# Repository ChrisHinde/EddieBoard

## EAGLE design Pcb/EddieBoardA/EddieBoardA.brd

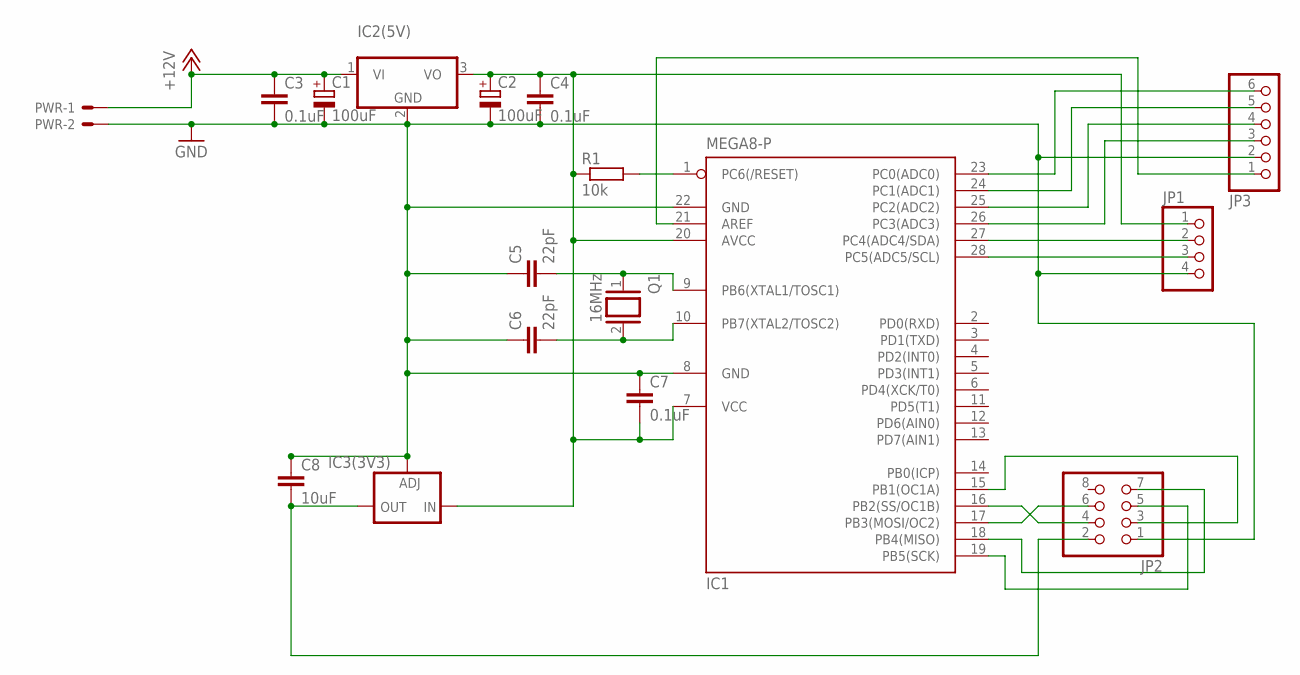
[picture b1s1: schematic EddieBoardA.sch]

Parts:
C1, C2: 100uF; E2,5-6
C3, C4, C7: 0.1uF; C025-025X050
C5, C6: 22pF; C025-025X050
C8: 10uF; C025-025X050
IC1: MEGA8-P; DIL28-3
IC2(5V): 7805TV; TO220V
IC3(3V3): LD117AV; TO220L1
JP1: PINHD-1X4; 1X04
JP2: PINHD-2X4; 2X04
JP3: PINHD-1X6; 1X06
PWR: 22-23-2021; MPN PWR
Q1: 16MHz; QS
R1: 10k; 0207/12

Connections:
+12V: C1.+, C3.1, IC2(5V).1 (VI), PWR.1
GND: C1.-, C2.-, C3.2, C4.2, C5.1, C6.1, C7.1, C8.1, IC1.8 (GND), IC1.22 (GND), IC2(5V).2 (GND), IC3(3V3).1 (ADJ), JP1.4, JP2.1, JP3.2, PWR.2
unnamed: IC1.1 (PC6(/RESET)), R1.2
unnamed: IC1.27 (PC4(ADC4/SDA)), JP1.2
unnamed: C5.2, IC1.9 (PB6(XTAL1/TOSC1)), Q1.1
unnamed: C6.2, IC1.10 (PB7(XTAL2/TOSC2)), Q1.2
unnamed: IC1.28 (PC5(ADC5/SCL)), JP1.3
unnamed: IC1.19 (PB5(SCK)), JP2.5
unnamed: IC1.15 (PB1(OC1A)), JP2.3
unnamed: IC1.17 (PB3(MOSI/OC2)), JP2.6
unnamed: IC1.16 (PB2(SS/OC1B)), JP2.4
unnamed: IC1.18 (PB4(MISO)), JP2.7
unnamed: IC1.21 (AREF), JP3.1
unnamed: IC1.26 (PC3(ADC3)), JP3.3
unnamed: IC1.25 (PC2(ADC2)), JP3.4
unnamed: IC1.24 (PC1(ADC1)), JP3.5
unnamed: IC1.23 (PC0(ADC0)), JP3.6
unnamed: C8.2, IC3(3V3).2 (OUT), JP2.2
VCC: C2.+, C4.1, C7.2, IC1.7 (VCC), IC1.20 (AVCC), IC2(5V).3 (VO), IC3(3V3).3 (IN), JP1.1, R1.1

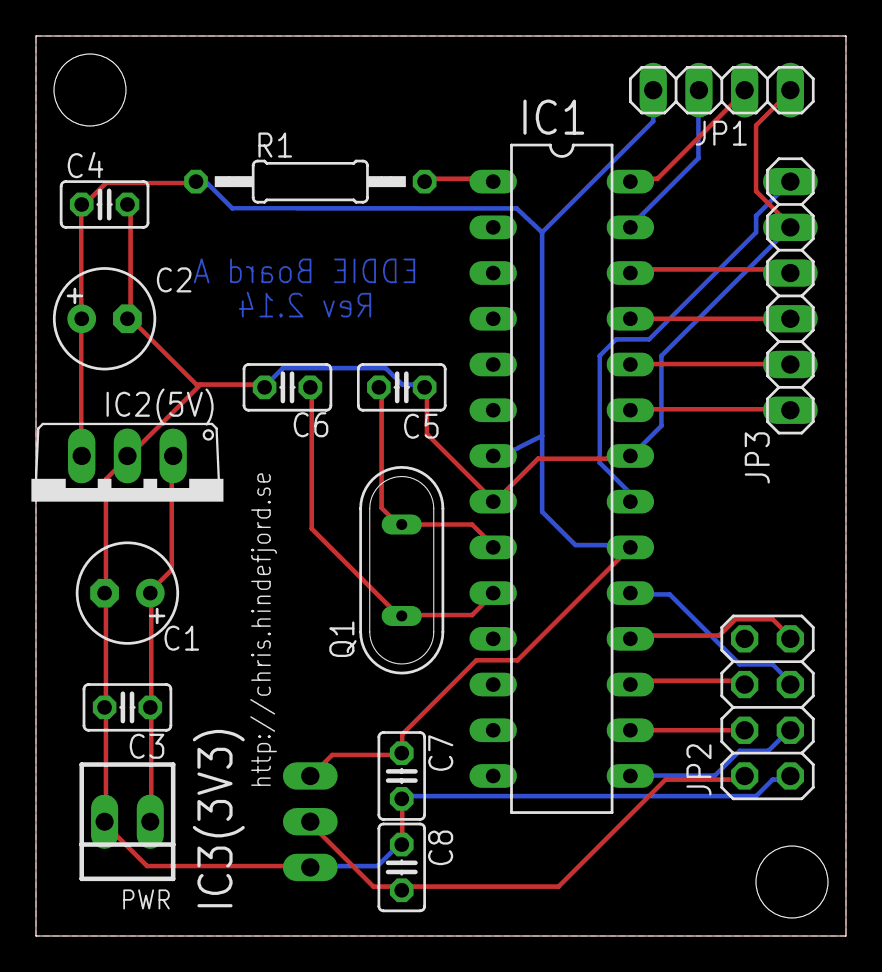
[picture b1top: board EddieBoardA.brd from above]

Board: 2 copper layers, 45.0 x 50.0 mm, 17 parts (0 on the bottom side), 19 nets.

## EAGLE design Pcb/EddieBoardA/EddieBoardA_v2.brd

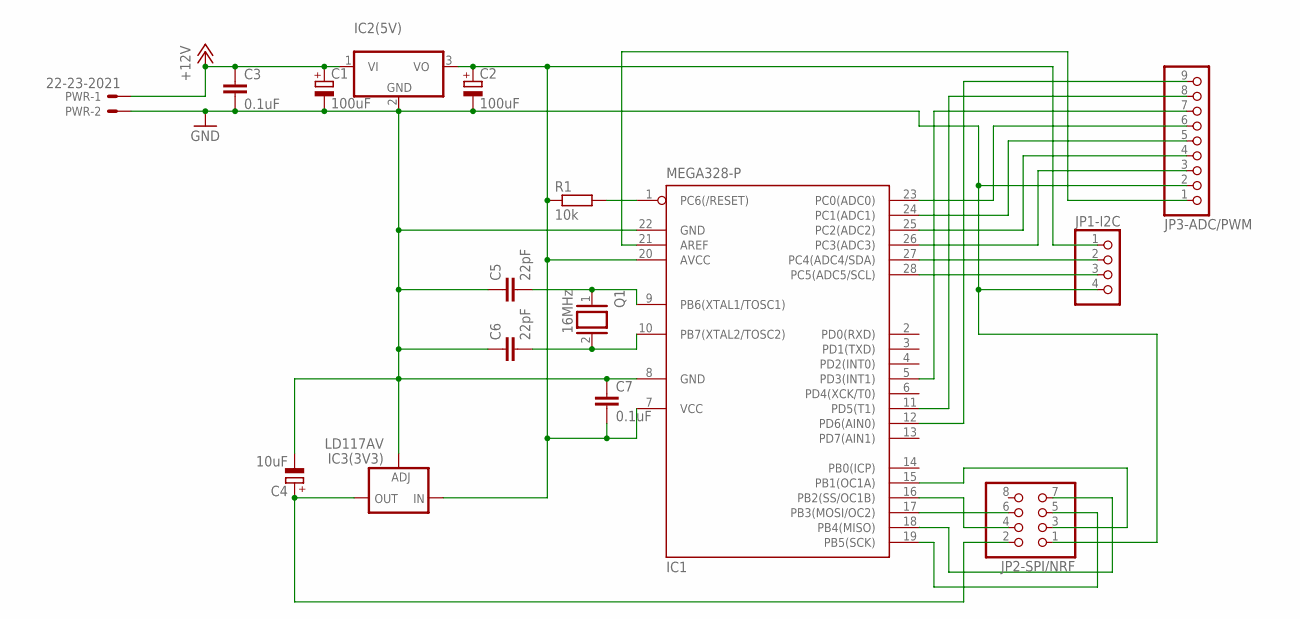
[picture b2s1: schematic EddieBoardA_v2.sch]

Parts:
C1, C2: 100uF; E2,5-6
C3, C7: 0.1uF; C025-025X050
C4: 10uF; E2,5-6
C5, C6: 22pF; C025-025X050
IC1: MEGA328-P; DIL28-3
IC2(5V): 7805TV; TO220V
IC3(3V3): LD117AV; TO220L1
JP1-I2C: PINHD-1X4; 1X04
JP2-SPI/NRF: PINHD-2X4; 2X04
JP3-ADC/PWM: PINHD-1X9; 1X09
PWR: 22-23-2021; MPN PWR
Q1: 16MHz; QS
R1: 10k; 0207/12

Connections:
3V3: C4.+, IC3(3V3).2 (OUT), JP2-SPI/NRF.2
+12V: C1.+, C3.1, IC2(5V).1 (VI), PWR.1
GND: C1.-, C2.-, C3.2, C4.-, C5.1, C6.1, C7.1, IC1.8 (GND), IC1.22 (GND), IC2(5V).2 (GND), IC3(3V3).1 (ADJ), JP1-I2C.4, JP2-SPI/NRF.1, JP3-ADC/PWM.2, PWR.2
MISO: IC1.18 (PB4(MISO)), JP2-SPI/NRF.7
MOSI: IC1.17 (PB3(MOSI/OC2)), JP2-SPI/NRF.6
unnamed: IC1.1 (PC6(/RESET)), R1.2
unnamed: C5.2, IC1.9 (PB6(XTAL1/TOSC1)), Q1.1
unnamed: C6.2, IC1.10 (PB7(XTAL2/TOSC2)), Q1.2
unnamed: IC1.15 (PB1(OC1A)), JP2-SPI/NRF.3
unnamed: IC1.21 (AREF), JP3-ADC/PWM.1
unnamed: IC1.26 (PC3(ADC3)), JP3-ADC/PWM.3
unnamed: IC1.25 (PC2(ADC2)), JP3-ADC/PWM.4
unnamed: IC1.24 (PC1(ADC1)), JP3-ADC/PWM.5
unnamed: IC1.23 (PC0(ADC0)), JP3-ADC/PWM.6
unnamed: IC1.5 (PD3(INT1)), JP3-ADC/PWM.7
unnamed: IC1.11 (PD5(T1)), JP3-ADC/PWM.8
unnamed: IC1.12 (PD6(AIN0)), JP3-ADC/PWM.9
SCK: IC1.19 (PB5(SCK)), JP2-SPI/NRF.5
SCL: IC1.28 (PC5(ADC5/SCL)), JP1-I2C.3
SDA: IC1.27 (PC4(ADC4/SDA)), JP1-I2C.2
SS: IC1.16 (PB2(SS/OC1B)), JP2-SPI/NRF.4
VCC: C2.+, C7.2, IC1.7 (VCC), IC1.20 (AVCC), IC2(5V).3 (VO), IC3(3V3).3 (IN), JP1-I2C.1, R1.1

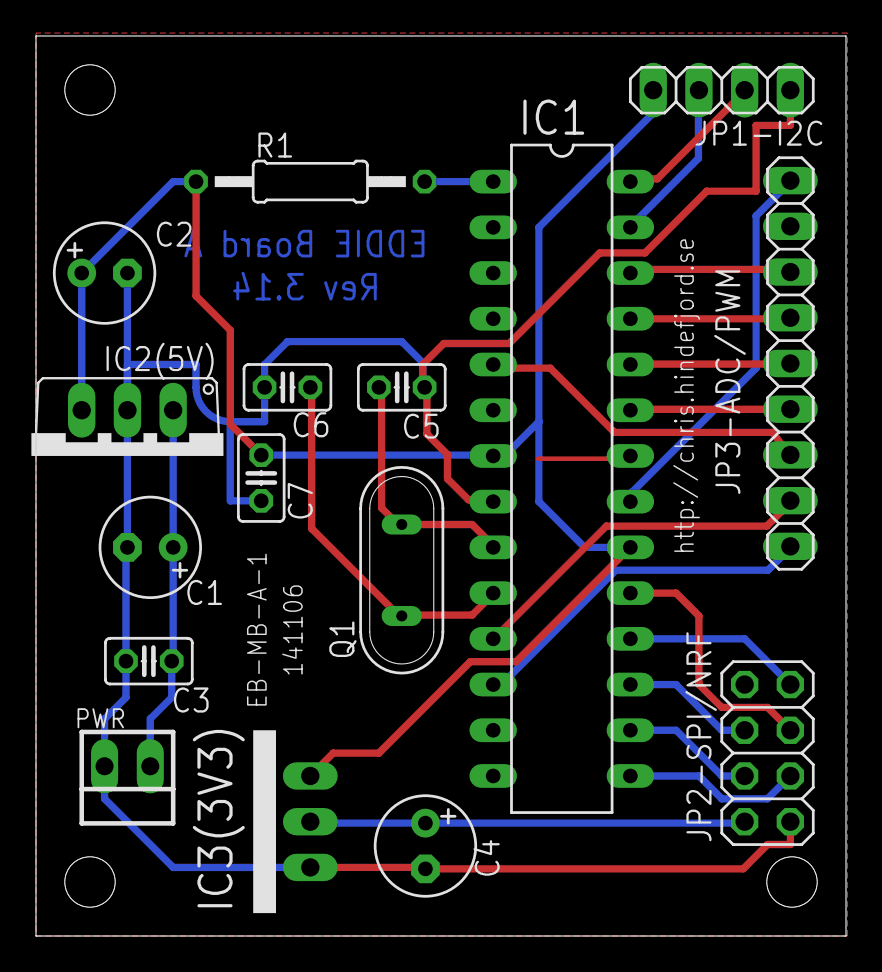
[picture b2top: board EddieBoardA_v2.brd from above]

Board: 2 copper layers, 45.0 x 50.0 mm, 16 parts (0 on the bottom side), 22 nets.

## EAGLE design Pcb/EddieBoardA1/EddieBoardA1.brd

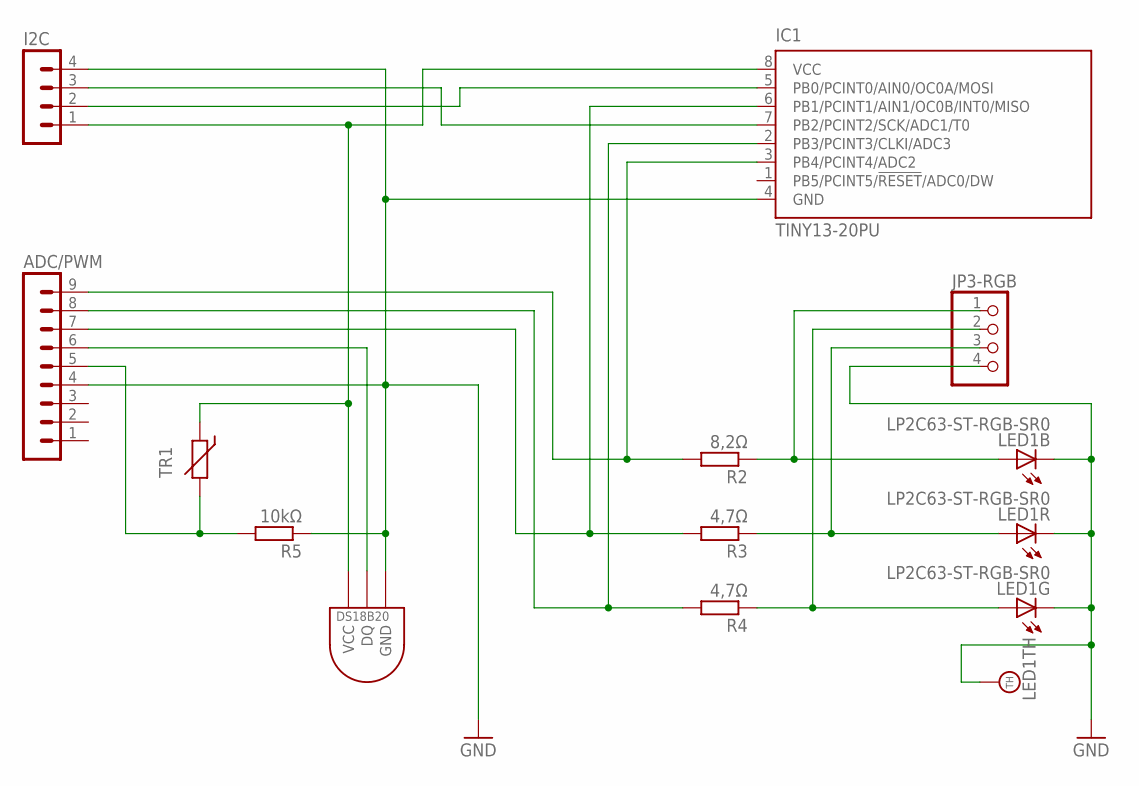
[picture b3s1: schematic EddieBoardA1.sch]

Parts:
ADC/PWM: MA09-1
I2C: MA04-1
IC1: TINY13-20PU; DIL08
JP3-RGB: PINHD-1X4; 1X04
LED1: LP2C63-ST-RGB-SR0
R2: 8,2Ω; 0204/7
R3, R4: 4,7Ω; 0204/7
R5: 10kΩ; 0204/7
TR1: THERMISTOR_R-5; R-5
U$1: DS1820TO92; DS1820

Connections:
GND: ADC/PWM.4, I2C.4, IC1.4 (GND), JP3-RGB.4, LED1.4 (C), LED1.5 (C), LED1.6 (C), LED1.TH, R5.1, U$1.GND
unnamed: ADC/PWM.6, U$1.DQ
unnamed: ADC/PWM.7, IC1.6 (PB1/PCINT1/AIN1/OC0B/INT0/MISO), R3.2
unnamed: ADC/PWM.8, IC1.2 (PB3/PCINT3/CLKI/ADC3), R4.2
unnamed: ADC/PWM.9, IC1.3 (PB4/PCINT4/ADC2), R2.2
unnamed: JP3-RGB.1, LED1.3 (A), R2.1
unnamed: JP3-RGB.3, LED1.2 (A), R3.1
unnamed: JP3-RGB.2, LED1.1 (A), R4.1
unnamed: ADC/PWM.5, R5.2, TR1.2
SCL: I2C.3, IC1.7 (PB2/PCINT2/SCK/ADC1/T0)
SDA: I2C.2, IC1.5 (PB0/PCINT0/AIN0/OC0A/MOSI)
VCC: I2C.1, IC1.8 (VCC), TR1.1, U$1.VDD (VCC)

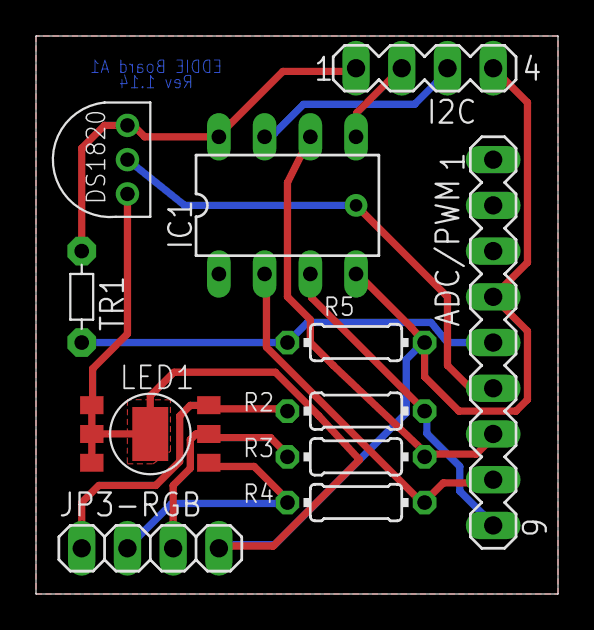
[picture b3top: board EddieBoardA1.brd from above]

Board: 2 copper layers, 29.0 x 31.0 mm, 11 parts (0 on the bottom side), 12 nets.

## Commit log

2014-11-14 :space_invader: Added .gitattributes & .gitignore files
2014-11-14 Move nrf24 code to subdirectory
2014-11-15 DHocument the code
    The whole project should now have clear comments on what's going on in
    the code!
